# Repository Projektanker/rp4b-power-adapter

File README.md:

# Raspberry Pi 4B Power Adapter

## Schematic

## PCB

## BOM
| Comment        | Designator | Footprint                                                 | LCSC Part | Alternative LCSC Part |
|----------------|------------|-----------------------------------------------------------|-----------|-----------------------|
| SMBJ5.0A       | F1         | Diode_SMD:D_SMB                                           | C10204    |                       |
| 5K1            | R1,R2      | Resistor_SMD:R_0603_1608Metric                            | C23186    |                       |
| TYPE-C-31-M-12 | X1         | Connector_USB:USB_C_Receptacle_HRO_TYPE-C-31-M-12         | C165948   |                       |
| FH-00339       | X2         | Connector_Harwin:Harwin_M20-7812045_2x20_P2.54mm_Vertical | C2685112  | C2685115, C2685092    |

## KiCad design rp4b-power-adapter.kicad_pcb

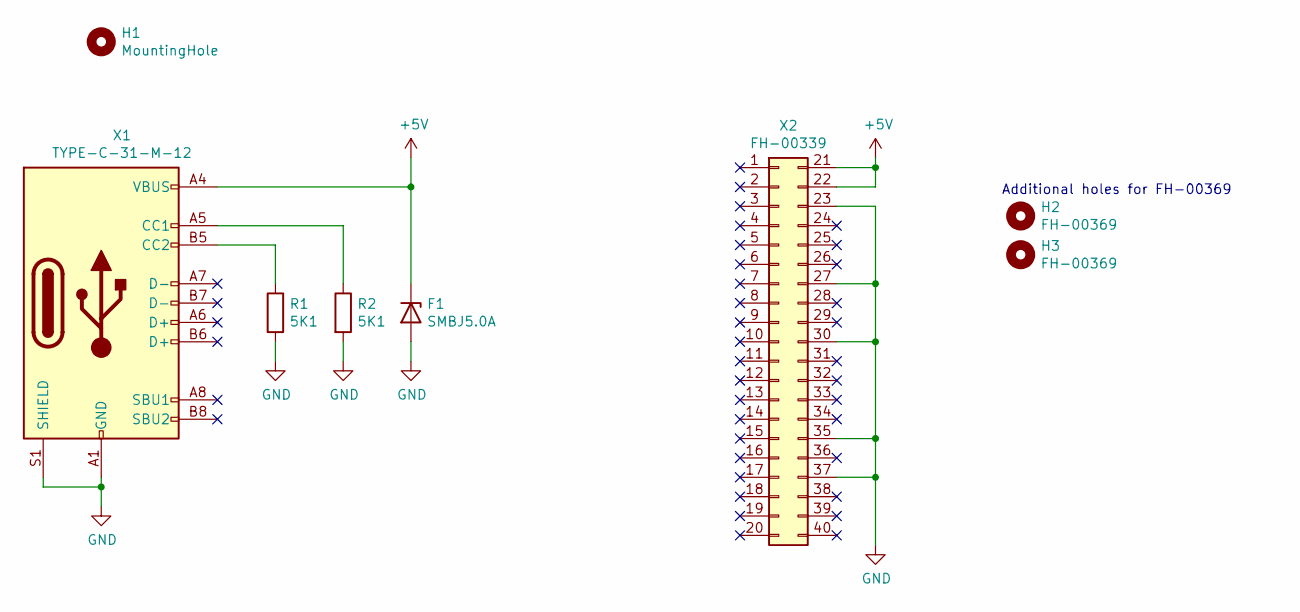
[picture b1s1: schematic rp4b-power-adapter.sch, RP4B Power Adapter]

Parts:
F1: SMBJ5.0A; D_SMB; MPN SMBJ5.0A-Q
H1: MountingHole; MountingHole_2.7mm
H2, H3: FH-00369; Hole_1.8mm
R1, R2: 5K1; R_0603_1608Metric
X1: TYPE-C-31-M-12; USB_C_Receptacle_HRO_TYPE-C-31-M-12; MPN TYPE-C-31-M-12
X2: FH-00339; Harwin_M20-7812045_2x20_P2.54mm_Vertical; MPN FH-00339

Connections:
+5V: F1.1 (K), X1.A4 (VBUS), X1.A9 (VBUS), X1.B4 (VBUS), X1.B9 (VBUS), X2.21, X2.22
GND: F1.2 (A), R1.2, R2.2, X1.A1 (GND), X1.A12 (GND), X1.B1 (GND), X1.B12 (GND), X1.S1 (SHIELD), X2.23, X2.27, X2.30, X2.35, X2.37
unnamed: R1.1, X1.B5 (CC2)
unnamed: R2.1, X1.A5 (CC1)

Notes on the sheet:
Additional holes for FH-00369

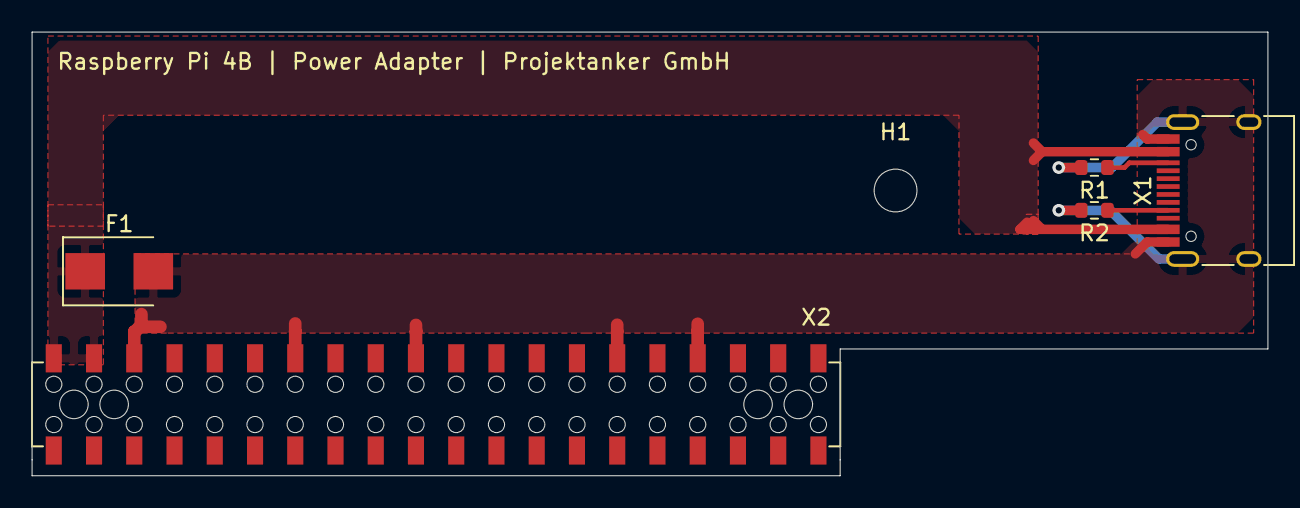
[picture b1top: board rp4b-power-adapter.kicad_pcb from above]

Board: 2 copper layers, 78.0 x 28.0 mm, 8 parts (0 on the bottom side), 4 nets.

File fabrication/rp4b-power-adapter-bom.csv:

Comment,Designator,Footprint,LCSC
"SMBJ5.0A","F1","Diode_SMD:D_SMB","C10204"
"5K1","R1,R2","Resistor_SMD:R_0603_1608Metric","C23186"
"TYPE-C-31-M-12","X1","Connector_USB:USB_C_Receptacle_HRO_TYPE-C-31-M-12","C165948"
"FH-00339","X2","Connector_Harwin:Harwin_M20-7812045_2x20_P2.54mm_Vertical","C2685112"

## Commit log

2021-11-01 Initial version
2021-11-01 Updates README
2021-11-01 Add white bg to schematic
2021-11-03 fixes F1 rotation
2021-11-13 Add additional holes for FH-00369 and alternatives for FH-00339 (FH-00369, FH-00148)
